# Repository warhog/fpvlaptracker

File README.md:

# fpvlaptracker

master: 

dev: 

licensed under [MIT](LICENSE.md)

open source diy fpv vtx lap tracking system

## features
- uses your analog vtx to do the lap detection
- 48 channels supported
- standalone (app) or connected mode (web frontend) available for single practicing or fun with friends
- connected mode supports up to 8 tracker units and comfortable access using web ui
- 2ms accuracy (tested with 4 parallel nodes)

## how does it work?
the tracker unit measures the video signal strength (rssi) of the selected video channel to detect laps using peak detection. it has a stand alone mode for single participants or a connected mode supporting multiple participants and a web ui. in standalone mode the tracker unit is controlled using bluetooth and a mobile app for configuration and single user race (e.g. practicing). the connected mode is used with any hardware that can run the java software backend.

### app
the tracker unit is accessed using bluetooth and a mobile application (older version was creating an wifi ap and serving a webpage but that was horrible slow). using the app one can configure the unit or run single user races (e.g. practicing).

the application is available in the play store (only android right now, [play store](https://play.google.com/store/apps/details?id=de.warhog.fpvlaptracker)), the source is in the app folder).

### standalone mode
the tracker can be used in standalone mode for single user races. only one tracker node and the app is needed.

### connected mode
running in the connected mode the tracker connects to a host software using wifi. races and particpants can be organized inside the host software. the host software includes a webserver that serves a web ui for watching / controlling races. one to multiple (max. 8) tracker nodes and server with wifi (e.g. raspi) required.

## tested devices
* immersion rc vtx
* blade inductrix fpv
* boscam ts5828
* eachine et526
* tbs unify pro hv
* betafpv 75s

## setup
[setup instructions](docs/setup.md)
    
## which hardware and software is used?
the hardware consists of a esp32 board with a boscam rx5808 receiver module connected. the esp32 runs the tracker firmware (written using Arduino software platform).
the backend of the race software for connected mode was written in java using spring boot 2. the frontend was developed using angular 8. the race software can be run on almost every platform that supports java se.
due to the low price, simplicity and size a raspberry pi (>= 2) powered by a power bank is the optimum solution for mobile usage.

# repository information
this repository contains everything needed to build your own tracker(s).

* app: the mobile app
* firmware: firmware for a single node
* hardware: hardware for a single node
* web: the java backend and web frontend for multiple node races

## sound files used
_lap:_ [freesound](https://www.freesound.org/people/StaneStane/sounds/73560/)

texts: [fromtexttospeech.com](http://www.fromtexttospeech.com/)

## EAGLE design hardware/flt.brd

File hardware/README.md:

# fpvlaptracker

this is the currently used hardware platform based on esp32 and rx5808.

for firmware building and flashing [read this](../docs/firmware.md)

## pictures

## schematics
the schematics and pcb are drawn using KiCAD5 (see schematics folder).

[pdf schematics](https://raw.githubusercontent.com/warhog/fpvlaptracker/master/hardware/schematics/schematic.pdf)

## bom (bill of material)

most of the pcb parts are found in the [bom csv file](https://github.com/warhog/fpvlaptracker/blob/master/hardware/fpvlaptracker32-bom.csv).

some additional parts are needed optionally:
* heatsink with 20x20 mm and heatsink glue for the rx5808
* 5v power supply board if you want to power from a LiPo, ..., i used the [pololu D24V10F5](https://www.pololu.com/product/2831) for this.

## housing

there is a 3d printable housing availbe in the housing folder. printing in pla with 0.2 mm layer height is enough. no supports needed.

## gerber files

if you want to make your own pcb you can use the gerber files in the gerber folder. i've used itead and elecrow and both were fine (itead is a bit cheaper, elecrow was quicker).

## rx5808 5,8 GHz receiver mod
the rx5808 receiver needs to be modified to support the SPI protocol.
an excellent description by shea ivey can be found [here](https://github.com/sheaivey/rx5808-pro-diversity/blob/master/docs/rx5808-spi-mod.md).

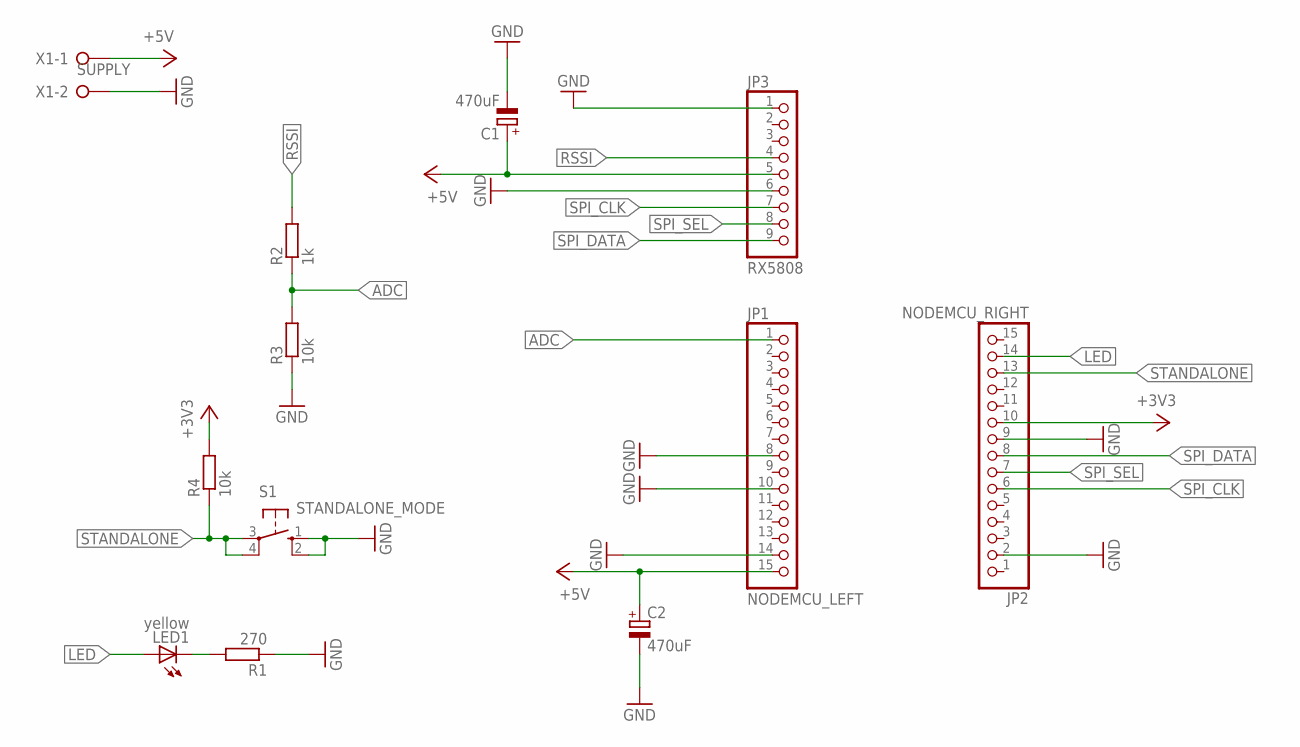
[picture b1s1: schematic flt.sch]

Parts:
C1, C2: 470uF; E5-8,5
JP1: NODEMCU_LEFT; 1X15
JP2: NODEMCU_RIGHT; 1X15
JP3: RX5808; 1X09
LED1: yellow; LED5MM
R1: 270; 0204/7
R2: 1k; 0204/7
R3, R4: 10k; 0204/7
S1: STANDALONE_MODE; B3F-10XX
X1: SUPPLY; W237-132

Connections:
+3V3: JP2.10, R4.2
+5V: C1.+, C2.+, JP1.15, JP3.5, X1.1
ADC: JP1.1, R2.1, R3.2
GND: C1.-, C2.-, JP1.8, JP1.10, JP1.14, JP2.2, JP2.9, JP3.1, JP3.6, R1.1, R3.1, S1.1 (S), S1.2 (S1), X1.2
LED: JP2.14, LED1.A
unnamed: LED1.K (C), R1.2
RSSI: JP3.4, R2.2
SPI_CLK: JP2.6, JP3.7
SPI_DATA: JP2.8, JP3.9
SPI_SEL: JP2.7, JP3.8
STANDALONE: JP2.13, R4.1, S1.3, S1.4 (P1)

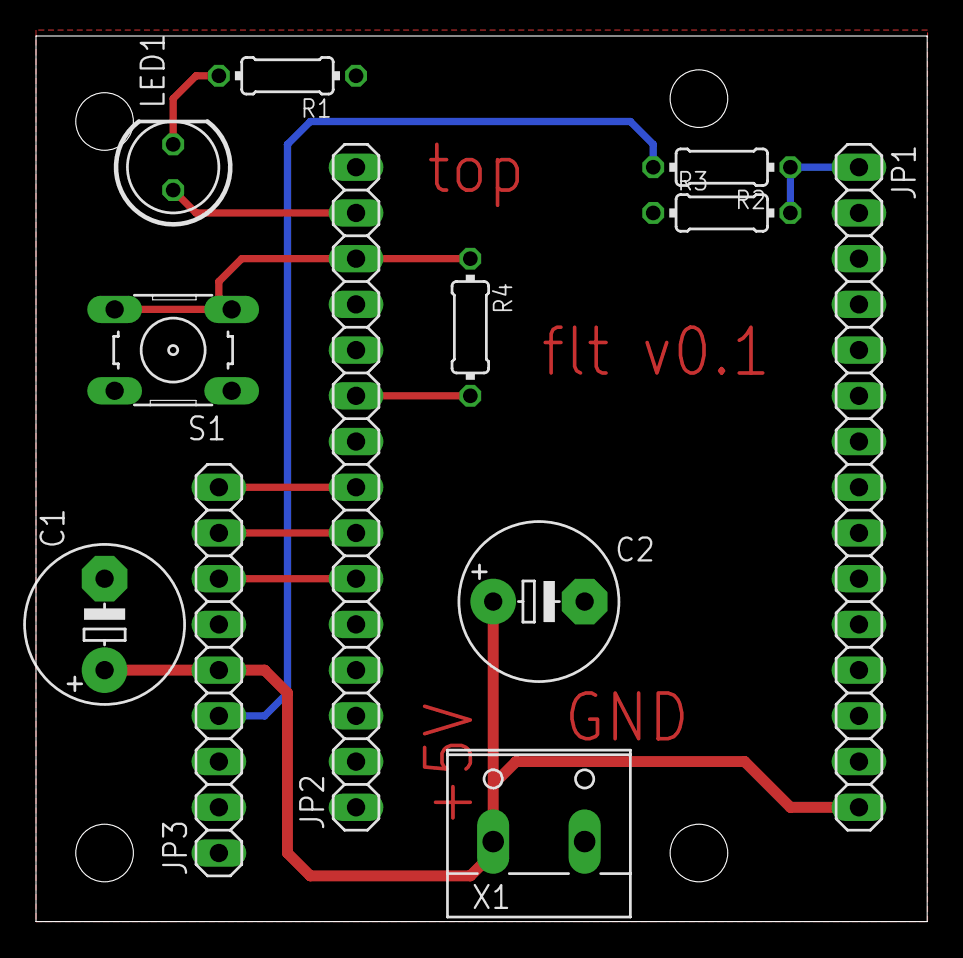
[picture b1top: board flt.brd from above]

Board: 2 copper layers, 49.5 x 49.2 mm, 12 parts (0 on the bottom side), 11 nets.

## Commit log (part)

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2017-04-23 initial code commit
2017-04-23 try to fix travis for multi language project
2017-04-23 fix gulp-sourcemaps issue again :)
2017-04-23 added missing gulp-rename to node config
2017-04-23 try to force new node version
2017-04-23 change before_install
2017-04-23 build jooq schema sources before build
2017-04-23 remove jooq generation from build task
2017-04-23 rename raceservice to racedbservice
2017-04-26 introduction of participant race service
2017-04-26 moved racestate to entities
2017-05-07 Create base_rpi
2017-05-23 many improvements in audio handling
2017-08-15 added multi language audio
2017-08-15 added hardware folder, added stl files for case
2017-08-22 improved audio service
2017-08-22 register as bluetooth unit
2017-08-25 refactoring of firmware code
2017-09-09 Rename configuration to configuration.md
2017-10-15 bump to version 0.2
2017-10-31 added channel scanner
2018-06-29 first draft of new bluetooth node firmware
2018-06-30 added serial communication to app, improved bt init on soft reset, made frequency class singleton
2018-07-10 make name changeable on bluetooth trackers
2018-07-15 use functions from timeutil
2018-08-11 added fpvlaptracker32
2018-08-11 added rssi to bluetooth lap data, added runtimedata
2018-08-23 fix buffer overrun
2018-08-23 change webupdate port
2018-08-24 improved dataexchange, small fixes
2018-08-25 better chipid
2018-08-25 improve first data message handling
2018-08-25 added cell getter to blink the number of detected cells on startup
2018-08-26 new defaults for trigger threshold and calibration offset
2018-08-27 moved firmware to separate repo
2018-09-09 bump version to 0.4
2018-09-12 updated dependencies, bumped version
2018-09-13 removed hardware files
2018-10-03 full esp32 tracker support
2018-10-03 improve and fix reboot handling
2018-10-07 fixed save of defaultvref and minlaptime
2018-10-13 added udp thread status, added favicon
2018-10-19 improve exception handling to make sure udphandler does never quit
2018-10-26 removed audio files
2018-11-08 unsubscribe lap listener as well
2018-11-28 make restservice more robust update websocketconfig to implement websocketmessagebrokerconfigurer
2018-12-19 introduction of project version
2018-12-19 add paths to fix compilation from ide
2018-12-19 added example configuration file
2018-12-19 removed old theme file from gulp
2018-12-19 adaptions for bootstrap 4
2018-12-19 reorder items, add cell voltage
2018-12-19 scroll to top after save
2018-12-19 added lowbattery and message udp packets and handling
2018-12-19 changed badge color for race badge
2018-12-19 introduce release_files
2018-12-19 checkout at the end
2018-12-22 introduce language files
2018-12-22 improve subscription handling
2018-12-22 simplify message handling
2018-12-23 fixed removal of inactive tracker nodes added timeout for RestTemplate resolved findbugs warnings
2018-12-23 fix blocking speak method
2018-12-23 make permanent switchable for danger alerts
2018-12-23 copy language files on release
2019-02-23 first test of fixed races
2019-02-23 updated bootstrap
2019-03-08 added skip calibration feature
2019-03-08 added rssi text, fixed small issues with calibration skipping
2019-03-09 lots of changes...
2019-03-09 moved some classes
2019-03-09 added race aborted text
2019-03-09 don't show invalid laps on chart
2019-03-10 added additional status and duration for pilots based on modes
2019-03-10 change race mode using buttons instead ofselect
2019-03-10 fixed duration display
2019-03-10 added no profile text
2019-03-22 added basic installer, added systemd service instead of start script
2019-03-22 improve startup
2019-03-22 inplace sed, freshen files from zip
2019-03-22 removed user
2019-03-27 fixed toplist, fixed first lap issue with round based races, small fixes
2019-05-03 updated jquery
2019-05-28 use -o instead of -f (force overwrite) in installer
2019-07-18 combined single repos back into one repo
2019-07-18 changed folder names
2019-07-19 switch to gulp-inject-version2
2019-07-19 add .gradle to ignore list
2019-07-31 update gradle versions
2019-08-15 complete refactoring of web ui and backend, adaptions on firmware for those changes
2019-08-15 fix findbugs warnings
2019-08-15 fix sed call
2019-08-15 added autofocus directive, added autofocus to login, added shutdown delay, fix missing login error message
2019-08-22 added queue for udp packets for faster packet handling
2019-08-22 removed fastrssi mode
2019-08-25 fix rssi packet issue, added overlay to update, added ssid+password to data
2019-08-29 beta release of new app
2019-09-01 fix length of alerts on mobile devices
2019-09-01 fix fullscreen in device view, fix issue when no tracker selected
2019-09-16 reformat styles, added bold
2019-09-18 streamline versions to be 3.0 for app, web and firmware
2019-09-26 move build banner to header
2019-09-27 fix tree test
2019-09-27 fix tag detection in build scripts
2019-09-27 try to fix deployment
2019-09-27 add library versions
2019-09-27 fix missing application properties files due to gitignore error
2019-09-27 add chipid to mdns node name
2019-09-27 add title to node ui
2019-09-27 fix reboot from ui
2019-09-27 bump version to 3.1.0
2019-09-28 added rssi to node web ui improved version commit on node web ui changed web ui calls to node to /api added node factory defaults for webui fix nodesetup webui redirector change log level to info all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
2019-09-30 update node data on nodes overview
2019-09-30 fix wording for node count beeing pronounced as third instead of three.
2019-09-30 add node availability check
2019-10-01 add wifi settings to node ui, small improvements on webui
2019-10-01 update documentation
2019-10-01 improve loading on nodes screen, sync nodes access, add firmware zip deployment
2019-10-01 disable nodesetup on offline nodes
2019-10-02 enable debug mode
2019-12-29 Bump handlebars from 4.1.2 to 4.5.3 in /web/webpage
    Bumps [handlebars](https://github.com/wycats/handlebars.js) from 4.1.2 to 4.5.3.
    - [Release notes](https://github.com/wycats/handlebars.js/releases)
    - [Changelog](https://github.com/wycats/handlebars.js/blob/master/release-notes.md)
    - [Commits](https://github.com/wycats/handlebars.js/compare/v4.1.2...v4.5.3)
2020-03-15 Bump acorn from 5.7.3 to 5.7.4 in /web/webpage
    Bumps [acorn](https://github.com/acornjs/acorn) from 5.7.3 to 5.7.4.
    - [Release notes](https://github.com/acornjs/acorn/releases)
    - [Commits](https://github.com/acornjs/acorn/compare/5.7.3...5.7.4)
2020-04-03 Bump acorn from 6.3.0 to 6.4.1 in /app
    Bumps [acorn](https://github.com/acornjs/acorn) from 6.3.0 to 6.4.1.
    - [Release notes](https://github.com/acornjs/acorn/releases)
    - [Commits](https://github.com/acornjs/acorn/compare/6.3.0...6.4.1)
2020-04-16 Bump https-proxy-agent from 2.2.2 to 2.2.4 in /app
    Bumps [https-proxy-agent](https://github.com/TooTallNate/node-https-proxy-agent) from 2.2.2 to 2.2.4.
    - [Release notes](https://github.com/TooTallNate/node-https-proxy-agent/releases)
    - [Commits](https://github.com/TooTallNate/node-https-proxy-agent/compare/2.2.2...2.2.4)
2020-04-30 Bump jquery from 3.4.1 to 3.5.0 in /web/webpage
    Bumps [jquery](https://github.com/jquery/jquery) from 3.4.1 to 3.5.0.
    - [Release notes](https://github.com/jquery/jquery/releases)
    - [Commits](https://github.com/jquery/jquery/compare/3.4.1...3.5.0)
2020-06-07 Bump websocket-extensions from 0.1.3 to 0.1.4 in /web/webpage
    Bumps [websocket-extensions](https://github.com/faye/websocket-extensions-node) from 0.1.3 to 0.1.4.
    - [Release notes](https://github.com/faye/websocket-extensions-node/releases)
    - [Changelog](https://github.com/faye/websocket-extensions-node/blob/master/CHANGELOG.md)
    - [Commits](https://github.com/faye/websocket-extensions-node/compare/0.1.3...0.1.4)
2020-06-18 Bump angular from 1.7.9 to 1.8.0 in /web
    Bumps [angular](https://github.com/angular/angular.js) from 1.7.9 to 1.8.0.
    - [Release notes](https://github.com/angular/angular.js/releases)
    - [Changelog](https://github.com/angular/angular.js/blob/master/CHANGELOG.md)
    - [Commits](https://github.com/angular/angular.js/compare/v1.7.9...v1.8.0)
2020-07-17 Bump lodash from 4.17.14 to 4.17.19 in /web
    Bumps [lodash](https://github.com/lodash/lodash) from 4.17.14 to 4.17.19.
    - [Release notes](https://github.com/lodash/lodash/releases)
    - [Commits](https://github.com/lodash/lodash/compare/4.17.14...4.17.19)
2020-07-18 Bump lodash from 4.17.15 to 4.17.19 in /app
    Bumps [lodash](https://github.com/lodash/lodash) from 4.17.15 to 4.17.19.
    - [Release notes](https://github.com/lodash/lodash/releases)
    - [Commits](https://github.com/lodash/lodash/compare/4.17.15...4.17.19)
2020-07-31 Bump elliptic from 6.5.0 to 6.5.3 in /app
    Bumps [elliptic](https://github.com/indutny/elliptic) from 6.5.0 to 6.5.3.
    - [Release notes](https://github.com/indutny/elliptic/releases)
    - [Commits](https://github.com/indutny/elliptic/compare/v6.5.0...v6.5.3)
2020-09-10 Bump http-proxy from 1.17.0 to 1.18.1 in /app
    Bumps [http-proxy](https://github.com/http-party/node-http-proxy) from 1.17.0 to 1.18.1.
    - [Release notes](https://github.com/http-party/node-http-proxy/releases)
    - [Changelog](https://github.com/http-party/node-http-proxy/blob/master/CHANGELOG.md)
    - [Commits](https://github.com/http-party/node-http-proxy/compare/1.17.0...1.18.1)
2021-03-09 Bump elliptic from 6.5.0 to 6.5.4 in /app
    Bumps [elliptic](https://github.com/indutny/elliptic) from 6.5.0 to 6.5.4.
    - [Release notes](https://github.com/indutny/elliptic/releases)
    - [Commits](https://github.com/indutny/elliptic/compare/v6.5.0...v6.5.4)
2021-03-30 Bump y18n from 4.0.0 to 4.0.1 in /app
    Bumps [y18n](https://github.com/yargs/y18n) from 4.0.0 to 4.0.1.
    - [Release notes](https://github.com/yargs/y18n/releases)
    - [Changelog](https://github.com/yargs/y18n/blob/master/CHANGELOG.md)
    - [Commits](https://github.com/yargs/y18n/commits)
2021-04-30 Bump ssri from 6.0.1 to 6.0.2 in /app
    Bumps [ssri](https://github.com/npm/ssri) from 6.0.1 to 6.0.2.
    - [Release notes](https://github.com/npm/ssri/releases)
    - [Changelog](https://github.com/npm/ssri/blob/v6.0.2/CHANGELOG.md)
    - [Commits](https://github.com/npm/ssri/compare/v6.0.1...v6.0.2)
2021-05-08 Bump handlebars from 4.5.3 to 4.7.7 in /web/webpage
    Bumps [handlebars](https://github.com/wycats/handlebars.js) from 4.5.3 to 4.7.7.
    - [Release notes](https://github.com/wycats/handlebars.js/releases)
    - [Changelog](https://github.com/handlebars-lang/handlebars.js/blob/master/release-notes.md)
    - [Commits](https://github.com/wycats/handlebars.js/compare/v4.5.3...v4.7.7)
2021-05-08 Bump url-parse from 1.4.4 to 1.5.1 in /web
    Bumps [url-parse](https://github.com/unshiftio/url-parse) from 1.4.4 to 1.5.1.
    - [Release notes](https://github.com/unshiftio/url-parse/releases)
    - [Commits](https://github.com/unshiftio/url-parse/compare/1.4.4...1.5.1)
2021-05-08 Bump url-parse from 1.4.7 to 1.5.1 in /app
    Bumps [url-parse](https://github.com/unshiftio/url-parse) from 1.4.7 to 1.5.1.
    - [Release notes](https://github.com/unshiftio/url-parse/releases)
    - [Commits](https://github.com/unshiftio/url-parse/compare/1.4.7...1.5.1)
2021-05-10 Bump lodash from 4.17.15 to 4.17.21 in /web/webpage
    Bumps [lodash](https://github.com/lodash/lodash) from 4.17.15 to 4.17.21.
    - [Release notes](https://github.com/lodash/lodash/releases)
    - [Commits](https://github.com/lodash/lodash/compare/4.17.15...4.17.21)
